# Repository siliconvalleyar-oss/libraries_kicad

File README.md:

# KiCad Libraries

Librerías personalizadas para KiCad organizadas en tres categorías:

## Estructura

```
libraries_kicad/
├── symbols.kicad_sym      # Librería de símbolos (19 componentes)
├── footprints.pretty/      # Librería de footprints (80 patrones)
├── 3dmodels/              # Modelos 3D (14 modelos STEP)
└── .gitignore
```

## Librerías

### Símbolos (`symbols.kicad_sym`)

Componentes electrónicos para esquemáticos:

| Categoría | Componentes |
|-----------|-------------|
| ICs | 74HCT245D, DS2482S-100, LPCXPRESSO_LPC1769, PIC18F4620-E_P, SN75451BP |
| Módulos | MRF24J40MA, Raspberry Pi Pico, Raspberry Pi Pico W |
| Sensores | ALS31300EEJASR-500, HFBR-1531, HFBR-2531Z |
| Conectores | F31L-1A7H1-11024, F32R-1A7H1-11024, PIM100 |
| Alimentación | BAT-HLD-012-SMT, VI-264-EU-F2 |
| Memoria | M48T08-100PC1 |
| Diodos | SS34 |

### Footprints (`footprints.pretty/`)

Patrones de pads para PCB (80 total):

- **SMD**: SOIC, QFN, DFN, SOT, QFP (LQFP-32, TQFP-100), DIP
- **Conectores**: Pin headers (1x02 a 2x15, vert/horiz), USB, Barrel Jack, Pololu Breakout
- **Pasivos**: 0603, 0805, 1206, 2512 (R, C, D, L)
- **Especiales**: Raspberry Pi Pico/W/Zero, displays, oscillators, test points (connector_pin1)

### Modelos 3D (`3dmodels/`)

Modelos STEP para visualización en PCB:

- 74HCT245D, ALS31300EEJASR-500, BAT-HLD-012-SMT
- DS2482S-100, F31L-1A7H1-11024, F32R-1A7H1-11024
- HFBR-2531Z, M48T08-100PC1, PIC18F4620-E_P
- Raspberry Pi Pico, Raspberry Pi Pico W, SS34
- VI-264-EU-F2, SN75451BP

## Instalación en KiCad

### Símbolos
1. Copiar `symbols.kicad_sym` a `~/Documents/KiCad/symbols/`
2. En KiCad: Pref Preferences → Manage Symbol Libraries
3. Agregar nueva librería y seleccionar el archivo

### Footprints
1. Copiar la carpeta `footprints.pretty/` a `~/Documents/KiCad/footprints/`
2. En KiCad: Pref Preferences → Manage Footprint Libraries
3. Agregar nueva librería y seleccionar la carpeta

### Modelos 3D
1. Copiar archivos `.step` a `~/Documents/KiCad/3dmodels/`
2. Los modelos se asignan automáticamente a los footprints correspondientes

## Contribuir

1. Fork el repositorio
2. Crear branch (`git checkout -b feature/nuevo-componente`)
3. Commit (`git commit -m 'Agregar componente X'`)
4. Push (`git push origin feature/nuevo-componente`)
5. Abrir Pull Request

## Licencia

Librerías bajo licencia GPL v2+ (compatible con KiCad)

## Autor

**siliconvalleyar-oss** - siliconvalleyar@gmail.com

## Changelog

### v1.1.0
- Agregados 5 footprints desde PCB cnc_pic32: PinHeader 1x04/1x06-H, TQFP-100, Pololu, connector_pin1
- Total: 80 footprints

### v1.0.0
- Versión inicial con 19 símbolos, 75 footprints y 14 modelos 3D
- Eliminación de duplicados entre librerías
- Organización en estructura limpia

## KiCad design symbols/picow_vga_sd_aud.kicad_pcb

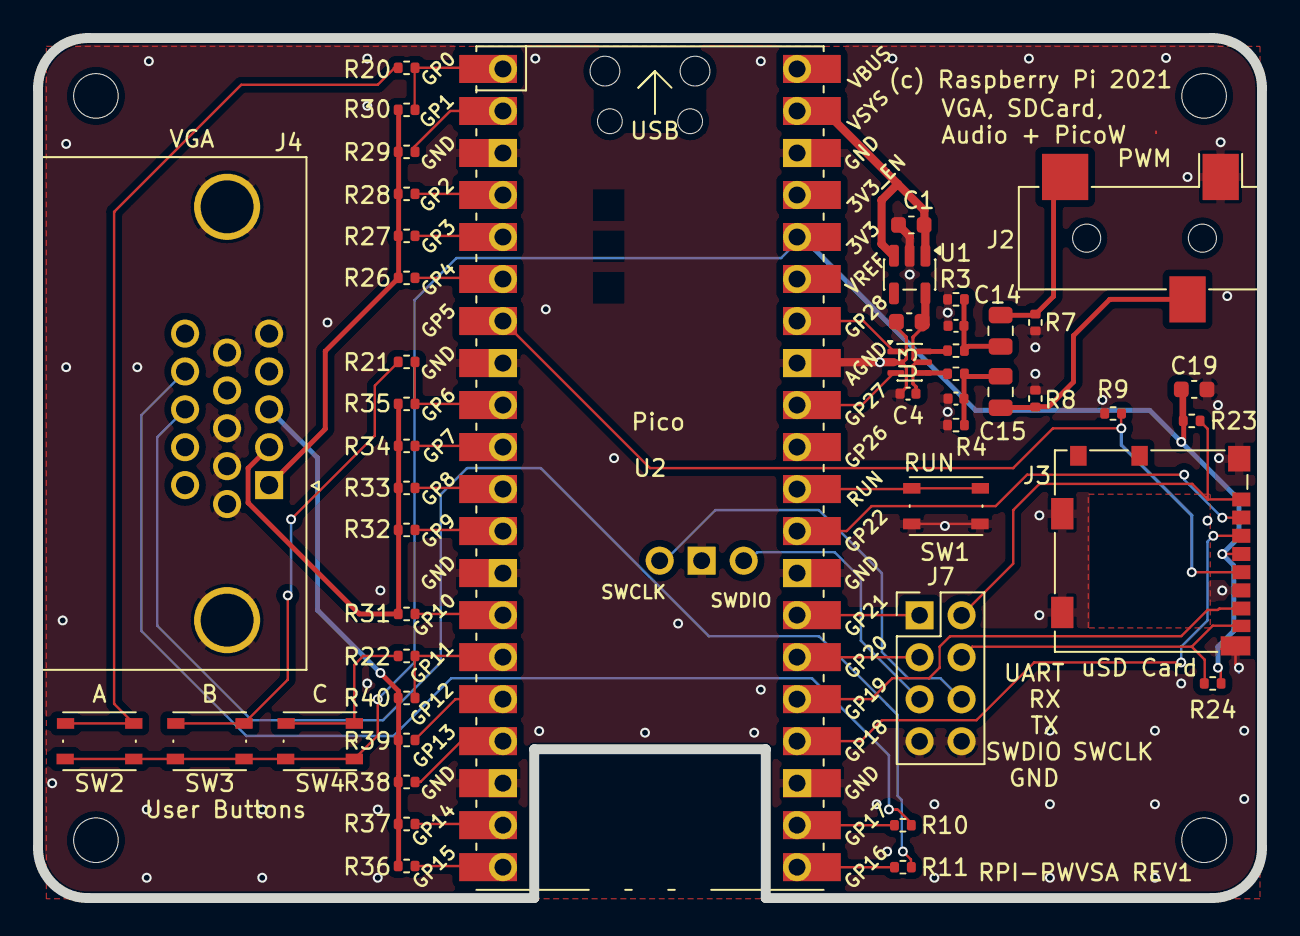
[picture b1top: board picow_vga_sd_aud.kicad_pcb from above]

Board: 4 copper layers, 74.0 x 52.0 mm, 52 parts (0 on the bottom side), 48 nets.

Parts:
C1, C2: 1u; C_0603_1608Metric
C4, C7, C8: 100n; C_0402_1005Metric
C14, C15: 47u; C_0805_2012Metric
C19: 10u; C_0603_1608Metric
H1, H2, H3, H4: MountingHole; MountingHole_2.7mm_M2.5
J2: AudioJack3; CUI_SJ-3523-audio-jack
J3: Micro_SD_Card; microSD_HC_Molex_104031-0811
J4: L77HDE15SD1CH4F; DSUB-15-L77HDE15SD1CH4F
J7: Conn_02x03_Odd_Even; PinHeader_2x04_P2.54mm_Vertical
R1, R2: 220; R_0402_1005Metric
R3, R4: 100; R_0402_1005Metric
R7, R8: 1.8K; R_0402_1005Metric
R9: DNF; R_0402_1005Metric
R10, R11: 47; R_0402_1005Metric
R20, R21, R22, R27, R32, R37: 1k; R_0402_1005Metric
R23, R24: 10k; R_0402_1005Metric
R26, R31, R36: 499; R_0402_1005Metric
R28, R33, R38: 2k; R_0402_1005Metric
R29, R34, R39: 4.02k; R_0402_1005Metric
R30, R35, R40: 8.06k; R_0402_1005Metric
SW1, SW2, SW3, SW4: SW_Push; SW_Push_1P1T_NO_Vertical_Wuerth_434133025816
U1: TLV70033_SOT23-5; SOT-23-5
U2: PicoW; RPi_PicoW_SMD_TH
U3: NC7WZ16P6X; SOT-363_SC-70-6

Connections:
+3.3VA: C2.1, C4.1, U1.5 (OUT), U3.5 (VCC)
+3V3: C19.1, J3.4 (VDD), R23.2, R24.2, SW2.1, SW3.1, SW4.1, U2.36 (3V3)
/GPIO0: R20.1, R30.2, U2.1 (GPIO0)
/GPIO1: R29.2, U2.2 (GPIO1)
/GPIO2: R28.2, U2.4 (GPIO2)
/GPIO3: R27.2, U2.5 (GPIO3)
/GPIO4: R26.2, U2.6 (GPIO4)
/GPIO5: J3.5 (CLK), R9.2, U2.7 (GPIO5)
/GPIO6: R21.1, R35.2, U2.9 (GPIO6)
/GPIO7: R34.2, U2.10 (GPIO7)
/GPIO8: R33.2, U2.11 (GPIO8)
/GPIO9: R32.2, U2.12 (GPIO9)
/GPIO10: R31.2, U2.14 (GPIO10)
/GPIO11: R22.1, R40.2, U2.15 (GPIO11)
/GPIO12: R39.2, U2.16 (GPIO12)
/GPIO13: R38.2, U2.17 (GPIO13)
/GPIO14: R37.2, U2.19 (GPIO14)
/GPIO15: R36.2, U2.20 (GPIO15)
/GPIO16: R11.2, U2.21 (GPIO16)
/GPIO17: R10.2, U2.22 (GPIO17)
/GPIO18: J3.3 (CMD), U2.24 (GPIO18)
/GPIO19: J3.7 (DAT0), U2.25 (GPIO19)
/GPIO20: J7.3, U2.26 (GPIO20)
/GPIO21: J7.1, U2.27 (GPIO21)
/GPIO22: J3.2 (DAT3/CD), U2.29 (GPIO22)
/GPIO27: U2.32 (GPIO27_ADC1), U3.3 (A2)
/GPIO28: U2.34 (GPIO28_ADC2), U3.1 (A1)
/HSYNC: J4.13, R11.1
/PWM_AUDIO_L: C14.1, J2.2 (T), R7.2
/PWM_AUDIO_R: C15.1, J2.3 (R), R8.2
/PWM_L: R1.2, U3.6 (Y1)
/PWM_LL: C7.1, C14.2, R1.1, R3.2
/PWM_R: R2.2, U3.4 (Y2)
/PWM_RR: C8.1, C15.2, R2.1, R4.2
/RUN: SW1.1, U2.30 (RUN)
/SD_DAT1: J3.8 (DAT1), J7.4, R24.1
/SD_DAT2: J3.1 (DAT2), J7.2, R23.1
/SWCLK: J7.6, U2.41 (SWCLK)
/SWDIO: J7.5, U2.43 (SWDIO)
/VGA_B: J4.3, R36.1, R37.1, R38.1, R39.1, R40.1
/VGA_G: J4.2, R31.1, R32.1, R33.1, R34.1, R35.1
/VGA_R: J4.1, R26.1, R27.1, R28.1, R29.1, R30.1
/VSYNC: J4.14, R10.1
/VSYS: C1.1, U1.1 (IN), U1.3 (EN), U2.39 (VSYS)
GND: C1.2, C2.2, C4.2, C7.2, C8.2, C19.2, J2.1 (S), J3.6 (VSS), J3.SH (SHIELD), J4.0, J4.5, J4.6, J4.7, J4.8, J4.10, J7.7, J7.8, R3.1, R4.1, R7.1, R8.1, R9.1, SW1.2, U1.2 (GND), U2.3 (GND), U2.8 (GND), U2.13 (GND), U2.18 (GND), U2.23 (GND), U2.28 (GND), U2.33 (AGND), U2.38 (GND), U2.42 (GND), U3.2 (GND)
unnamed: R20.2, SW2.2
unnamed: R21.2, SW3.2
unnamed: R22.2, SW4.2
